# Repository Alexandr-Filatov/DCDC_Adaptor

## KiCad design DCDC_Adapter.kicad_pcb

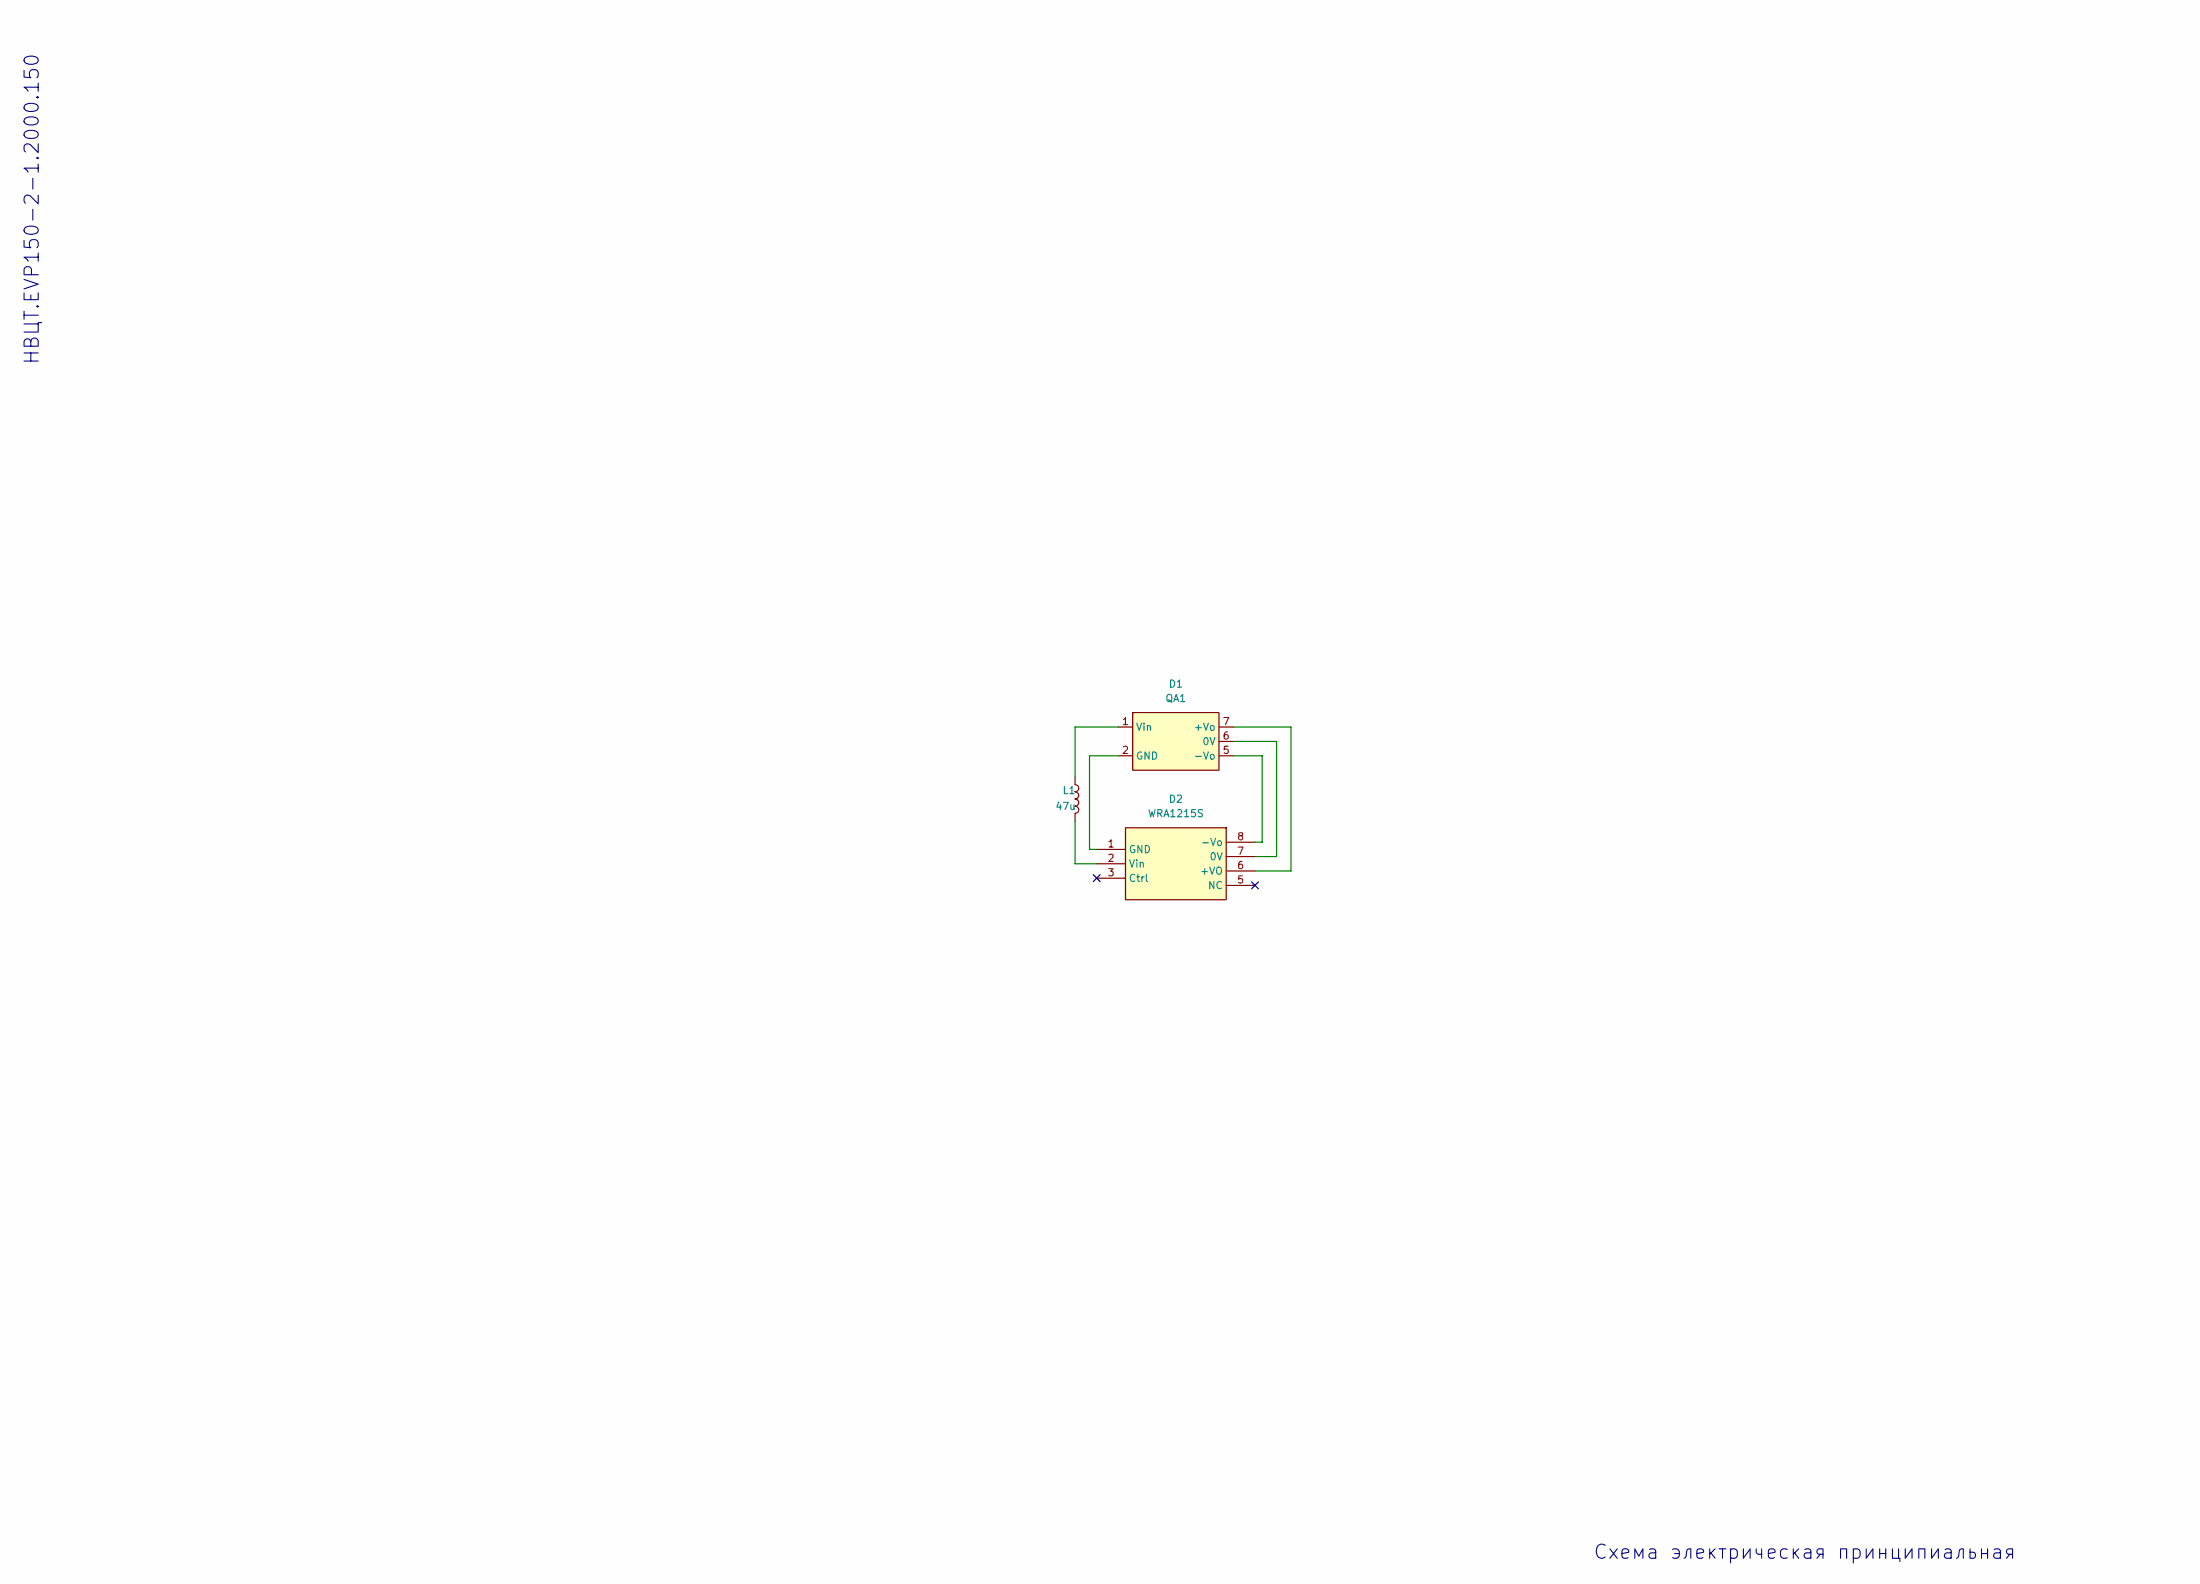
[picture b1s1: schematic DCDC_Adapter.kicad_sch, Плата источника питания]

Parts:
D1: QA1; QA
D2: WRA1215S; WRA_S-1WR2
L1: 47u; L_1812_4532Metric_Pad1.30x3.40mm_HandSolder

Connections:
unnamed: D1.6 (0V), D2.7 (0V)
unnamed: D1.7 (+Vo), D2.6 (+VO)
unnamed: D1.5 (-Vo), D2.8 (-Vo)
unnamed: D1.2 (GND), D2.1 (GND)
unnamed: D1.1 (Vin), L1.1
unnamed: D2.2 (Vin), L1.2

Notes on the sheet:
НВЦТ.EVP150-2-1.2000.150
Схема электрическая принципиальная

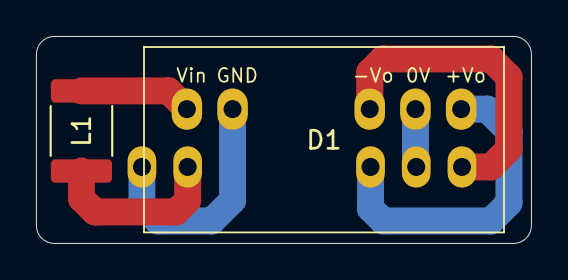
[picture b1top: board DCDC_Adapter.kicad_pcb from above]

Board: 2 copper layers, 27.5 x 11.5 mm, 3 parts (0 on the bottom side), 6 nets.

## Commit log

2025-05-28 zero commit
2025-07-10 VER1.0: добавил папку Docs
2025-07-14 VER1.0: исправил Э3
2025-07-16 VER1.0: сделал BOM и спеку
2025-07-16 VER1.0: исправил спеку
2025-07-16 VER1.0: исправил спеку еще раз
